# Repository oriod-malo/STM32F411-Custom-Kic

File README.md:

# STM32F411-Custom-Kit

#### NOTE (as of April 12th 2023)
#### By Kicad ERC and DRC this board should be functional however it's not manufactured yet for a physical, hands-on testing.

## Description

This is my first fully independent KiCad project after following the tutorial for the STM32F103.
A STM32F411 Discovery board was something I wanted to buy since a long time.
However, I figured out it's better if I learn to make myself something similar and have it assembled.<br>
<br>
Due to component density and pin count, this schematic ended up being a 6-layer board. <br>
<br>
Layer parameters and component choice has been made considering jlcpcb constraints and components library(for the sake of orientation). It can be manufactured by ANY service. <br>
Also feel free to change constraints / components. <br>
<br>
<br>

## Differences between this and actual Discovery Boards.

* Due to unavailability of components, I removed all the audio subsystem that Discovery boards have and replaced it with extra pins

* Again due to components availability some components have been replaced with others and / or similar components

* I have no idea how many layers Discovery Kits actually have, this one has 6 layers: Signal(F)/GND/Signal/Signal/Power/Signal(B)

## Installation
1. Create a project called "STM32 Discovery" in KiCad 7.0 (while this is NOT a Discovery kit the name persists from when I first created the project for orientation)

2. Copy all files <except for those in the (previous_sections_files)> from this Git inside the .../Documents/KiCad/7.0/projects/STM32 Discovery

3. Go to the folder "(previous_sections_files)" you will see two subfolders "3dmodels" and "footprints". Copy those in "/Documents/KiCad/7.0/3dmodels" and ""/Documents/KiCad/7.0/footprints" respectively

## Screenshoots

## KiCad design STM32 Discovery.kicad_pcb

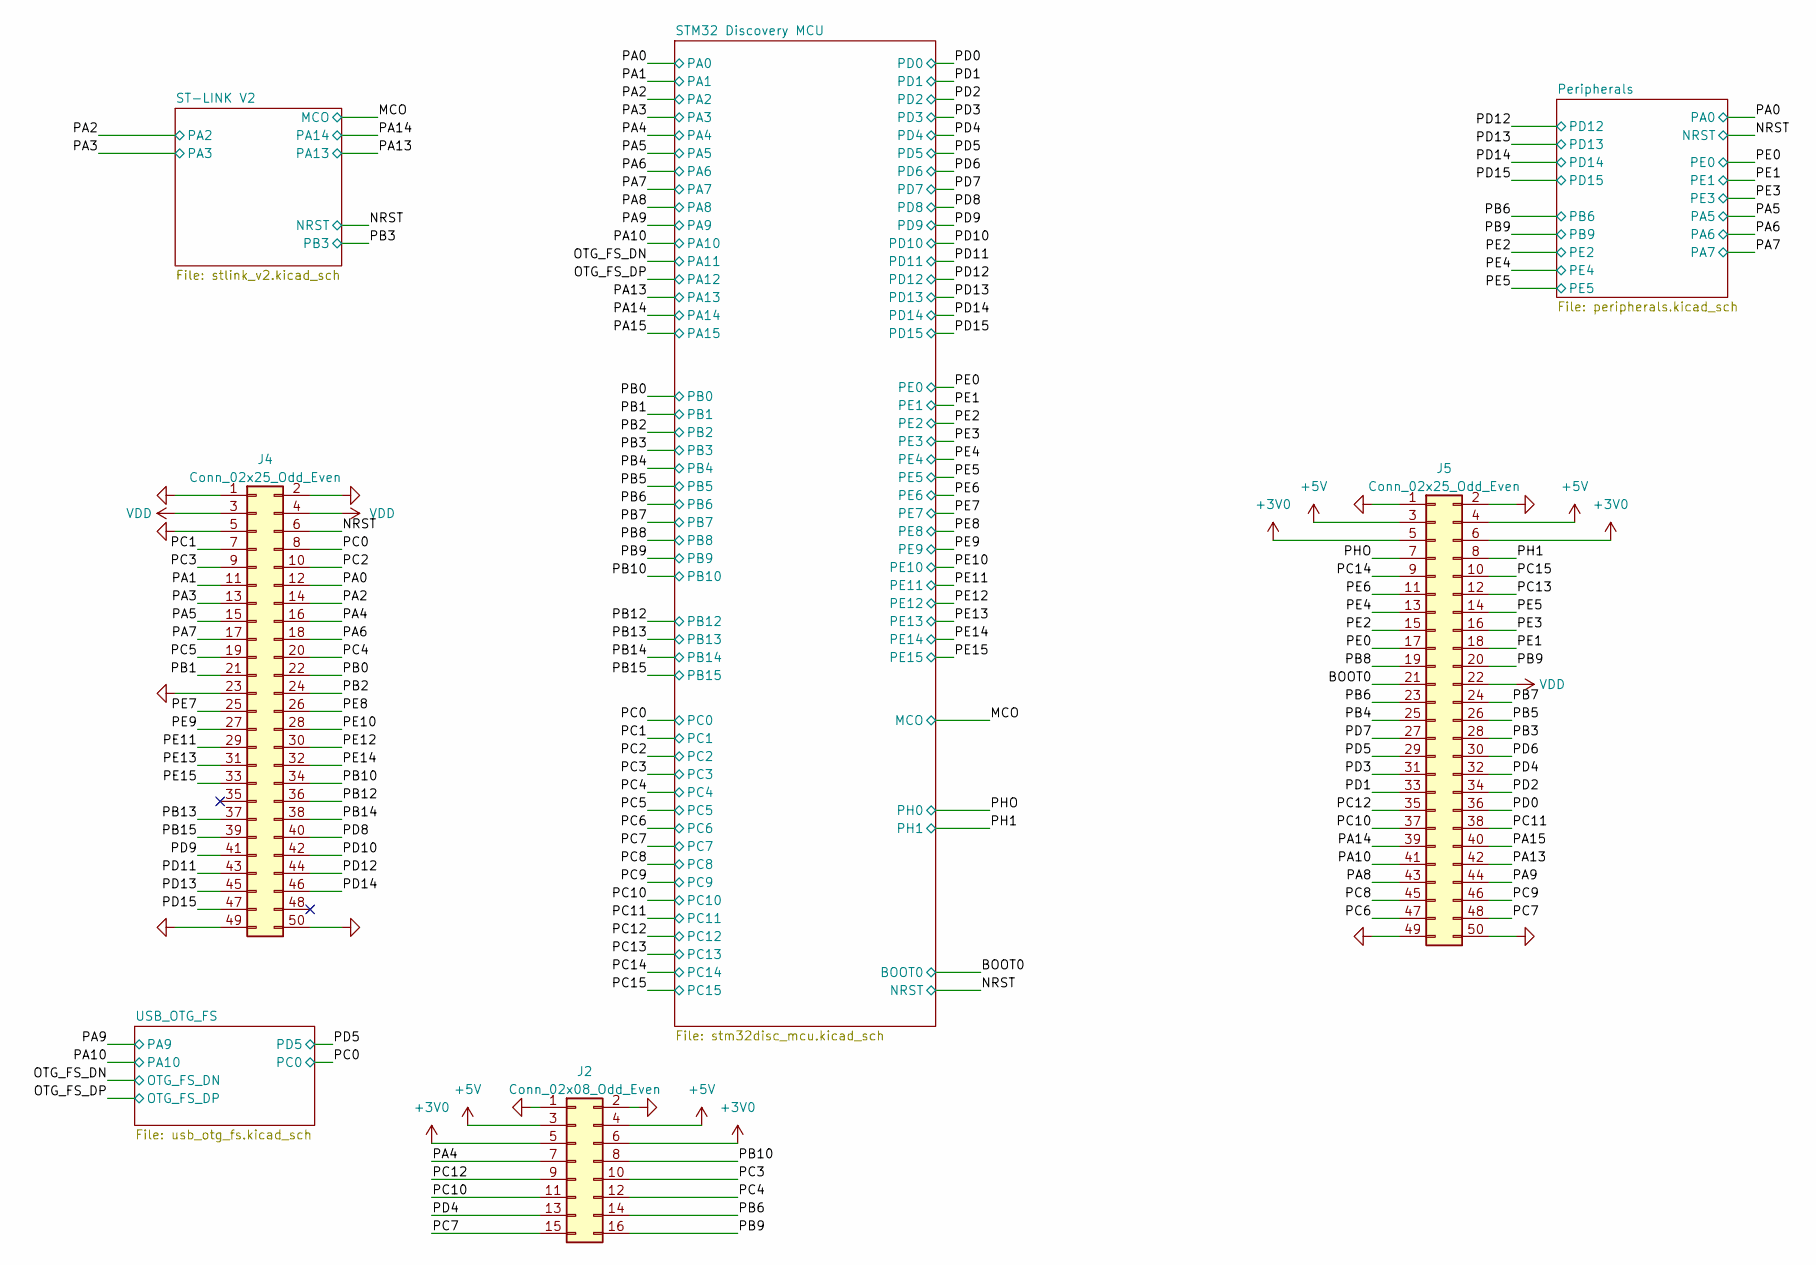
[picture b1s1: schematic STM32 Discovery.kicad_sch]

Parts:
J2: Conn_02x08_Odd_Even; PinHeader_2x08_P2.54mm_Vertical
J4, J5: Conn_02x25_Odd_Even; PinHeader_2x25_P2.54mm_Vertical

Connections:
+3V0: J2.5, J2.6, J5.5, J5.6; also elsewhere on the board
+5V: J2.3, J2.4, J5.3, J5.4; also elsewhere on the board
/BOOT0: J5.21; also elsewhere on the board
/NRST: J4.6; also elsewhere on the board
/PA0: J4.12; also elsewhere on the board
/PA1: J4.11; also elsewhere on the board
/PA2: J4.14; also elsewhere on the board
/PA3: J4.13; also elsewhere on the board
/PA4: J2.7, J4.16; also elsewhere on the board
/PA5: J4.15; also elsewhere on the board
/PA6: J4.18; also elsewhere on the board
/PA7: J4.17; also elsewhere on the board
/PA8: J5.43; also elsewhere on the board
/PA9: J5.44; also elsewhere on the board
/PA10: J5.41; also elsewhere on the board
/PA13: J5.42; also elsewhere on the board
/PA14: J5.39; also elsewhere on the board
/PA15: J5.40; also elsewhere on the board
/PB0: J4.22; also elsewhere on the board
/PB1: J4.21; also elsewhere on the board
/PB2: J4.24; also elsewhere on the board
/PB3: J5.28; also elsewhere on the board
/PB4: J5.25; also elsewhere on the board
/PB5: J5.26; also elsewhere on the board
/PB6: J2.14, J5.23; also elsewhere on the board
/PB7: J5.24; also elsewhere on the board
/PB8: J5.19; also elsewhere on the board
/PB9: J2.16, J5.20; also elsewhere on the board
/PB10: J2.8, J4.34; also elsewhere on the board
/PB12: J4.36; also elsewhere on the board
/PB13: J4.37; also elsewhere on the board
/PB14: J4.38; also elsewhere on the board
/PB15: J4.39; also elsewhere on the board
/PC0: J4.8; also elsewhere on the board
/PC1: J4.7; also elsewhere on the board
/PC2: J4.10; also elsewhere on the board
/PC3: J2.10, J4.9; also elsewhere on the board
/PC4: J2.12, J4.20; also elsewhere on the board
/PC5: J4.19; also elsewhere on the board
/PC6: J5.47; also elsewhere on the board
/PC7: J2.15, J5.48; also elsewhere on the board
/PC8: J5.45; also elsewhere on the board
/PC9: J5.46; also elsewhere on the board
/PC10: J2.11, J5.37; also elsewhere on the board
/PC11: J5.38; also elsewhere on the board
/PC12: J2.9, J5.35; also elsewhere on the board
/PC13: J5.12; also elsewhere on the board
/PC14: J5.9; also elsewhere on the board
/PC15: J5.10; also elsewhere on the board
/PD0: J5.36; also elsewhere on the board
/PD1: J5.33; also elsewhere on the board
/PD2: J5.34; also elsewhere on the board
/PD3: J5.31; also elsewhere on the board
/PD4: J2.13, J5.32; also elsewhere on the board
/PD5: J5.29; also elsewhere on the board
/PD6: J5.30; also elsewhere on the board
/PD7: J5.27; also elsewhere on the board
/PD8: J4.40; also elsewhere on the board
/PD9: J4.41; also elsewhere on the board
/PD10: J4.42; also elsewhere on the board
/PD11: J4.43; also elsewhere on the board
/PD12: J4.44; also elsewhere on the board
/PD13: J4.45; also elsewhere on the board
/PD14: J4.46; also elsewhere on the board
/PD15: J4.47; also elsewhere on the board
/PE0: J5.17; also elsewhere on the board
/PE1: J5.18; also elsewhere on the board
/PE2: J5.15; also elsewhere on the board
/PE3: J5.16; also elsewhere on the board
/PE4: J5.13; also elsewhere on the board
/PE5: J5.14; also elsewhere on the board
/PE6: J5.11; also elsewhere on the board
/PE7: J4.25; also elsewhere on the board
/PE8: J4.26; also elsewhere on the board
/PE9: J4.27; also elsewhere on the board
/PE10: J4.28; also elsewhere on the board
/PE11: J4.29; also elsewhere on the board
/PE12: J4.30; also elsewhere on the board
/PE13: J4.31; also elsewhere on the board
/PE14: J4.32; also elsewhere on the board
/PE15: J4.33; also elsewhere on the board
/PH1: J5.8; also elsewhere on the board
/PHO: J5.7; also elsewhere on the board
GND: J2.1, J2.2, J4.1, J4.2, J4.5, J4.23, J4.49, J4.50, J5.1, J5.2, J5.49, J5.50; also elsewhere on the board
VDD: J4.3, J4.4, J5.22; also elsewhere on the board

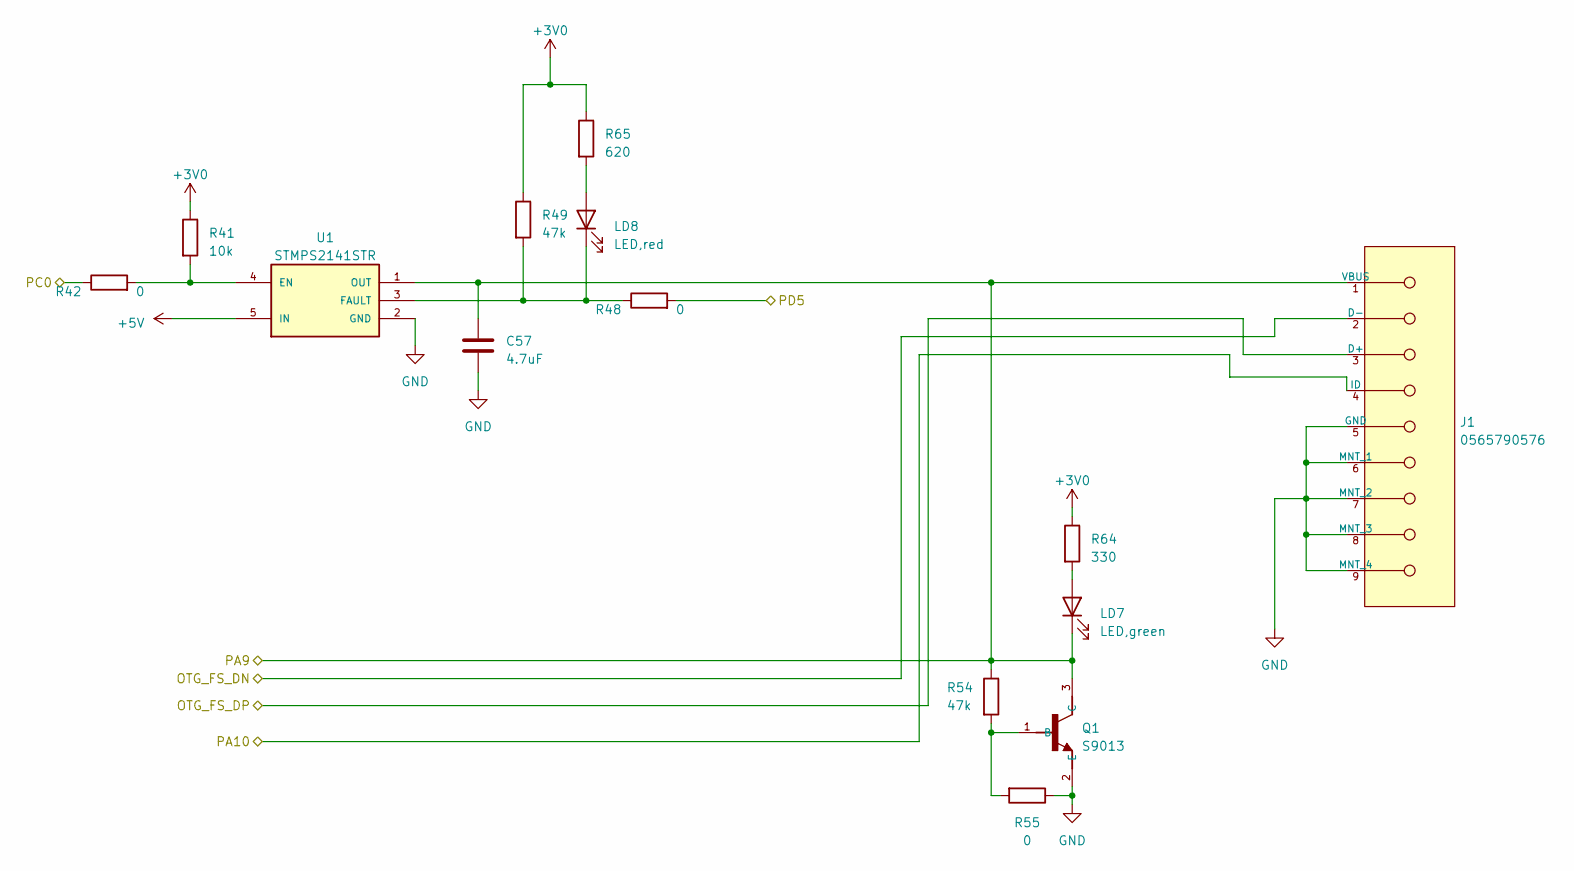
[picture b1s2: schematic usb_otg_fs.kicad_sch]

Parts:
C57: 4.7uF; C_0402_1005Metric
J1: 0565790576; Molex-0565790576-0; voltage 30VAC/DC; mouser part number 538-56579-0576; digikey description CONN RECEPT USB 5POS RT ANG SMD
LD7: LED,green; LED_0402_1005Metric
LD8: LED,red; LED_0402_1005Metric
Q1: S9013; SOT-23
R41: 10k; R_0402_1005Metric
R42, R48, R55: 0; R_0402_1005Metric
R49, R54: 47k; R_0402_1005Metric
R64: 330; R_0402_1005Metric
R65: 620; R_0402_1005Metric
U1: STMPS2141STR; SOT-23-5

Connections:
+3V0: R41.1, R49.1, R64.1, R65.1; also elsewhere on the board
+5V: U1.5 (IN); also elsewhere on the board
/OTG_FS_DN: J1.2 (D-); also elsewhere on the board
/OTG_FS_DP: J1.3 (D+); also elsewhere on the board
/PA9: C57.1, J1.1 (VBUS), LD7.1 (K), Q1.3 (C), R54.1, U1.1 (OUT); also elsewhere on the board
/PA10: J1.4 (ID); also elsewhere on the board
/PC0: R42.1; also elsewhere on the board
/PD5: R48.2; also elsewhere on the board
GND: C57.2, J1.5 (GND), J1.6 (MNT_1), J1.7 (MNT_2), J1.8 (MNT_3), J1.9 (MNT_4), Q1.2 (E), R55.1, U1.2 (GND); also elsewhere on the board
unnamed: LD7.2 (A), R64.2
unnamed: LD8.2 (A), R65.2
unnamed: LD8.1 (K), R48.1, R49.2, U1.3 (FAULT)
unnamed: Q1.1 (B), R54.2, R55.2
unnamed: R41.2, R42.2, U1.4 (EN)

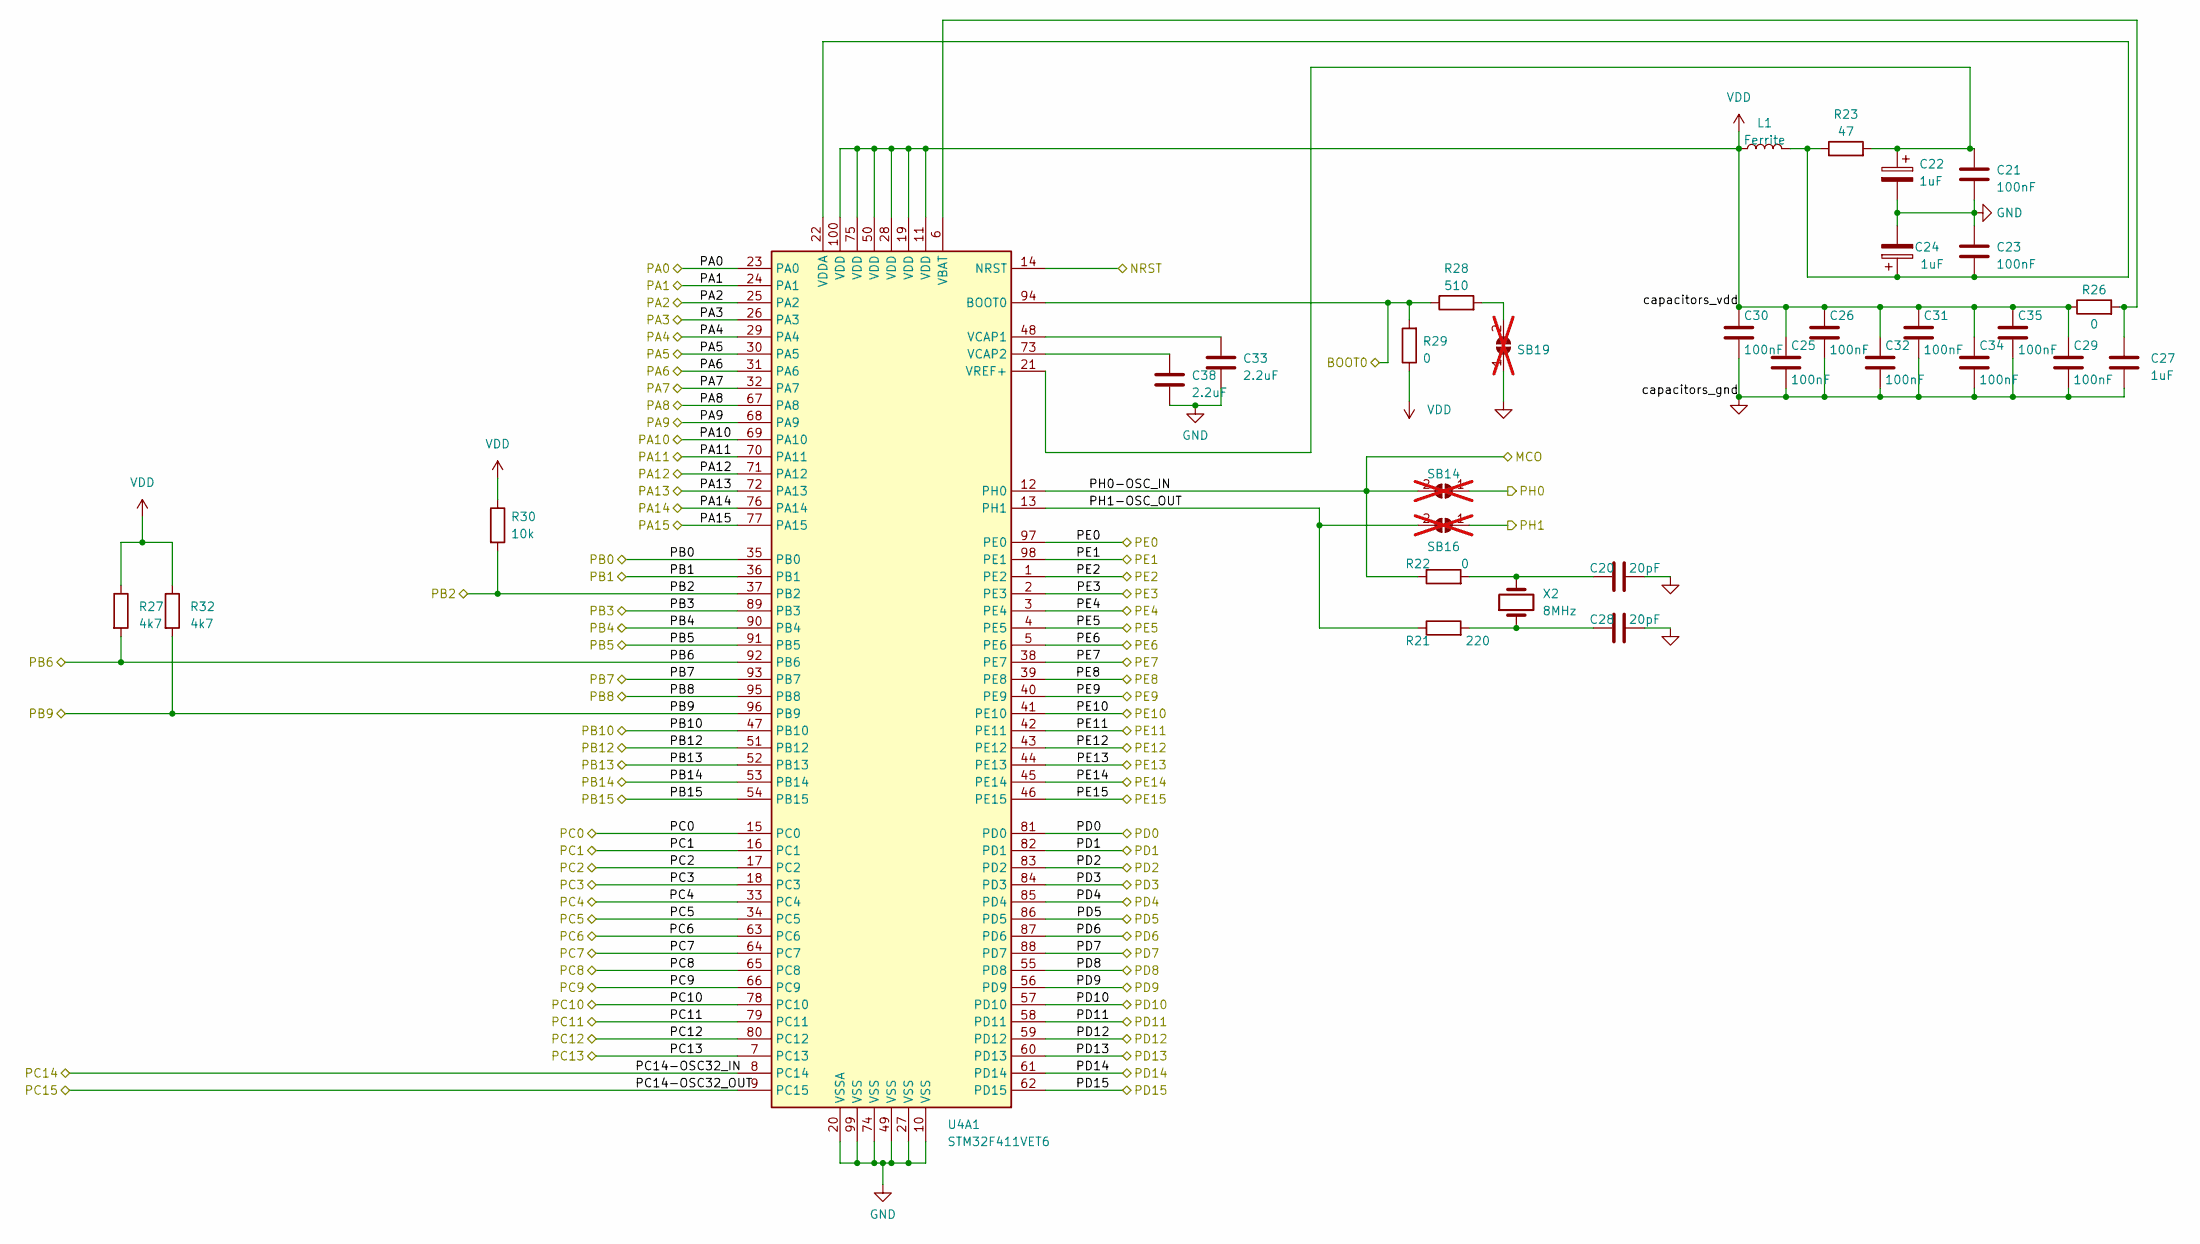
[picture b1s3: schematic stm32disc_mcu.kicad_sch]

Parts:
C20, C28: 20pF; C_0402_1005Metric
C21, C23, C25, C26, C29, C30, C31, C32, C34, C35: 100nF; C_0402_1005Metric
C22, C24, C27: 1uF; C_0402_1005Metric
C33, C38: 2.2uF; C_0402_1005Metric
L1: Ferrite; L_0603_1608Metric
R21: 220; R_0402_1005Metric
R22, R26, R29: 0; R_0402_1005Metric
R23: 47; R_0402_1005Metric
R27, R32: 4k7; R_0402_1005Metric
R28: 510; R_0402_1005Metric
R30: 10k; R_0402_1005Metric
SB14, SB16, SB19: SolderJumper_2_Open; SolderJumper-2_P1.3mm_Open_TrianglePad1.0x1.5mm; not fitted
U4A1: STM32F411VET6; LQFP-100_14x14mm_P0.5mm
X2: 8MHz; Crystal_SMD_5032-2Pin_5.0x3.2mm

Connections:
/BOOT0: R28.1, R29.2, U4A1.94 (BOOT0); also elsewhere on the board
/MCO: R22.1, SB14.2 (B), U4A1.12 (PH0); also elsewhere on the board
/NRST: U4A1.14 (NRST); also elsewhere on the board
/OTG_FS_DN: U4A1.70 (PA11); also elsewhere on the board
/OTG_FS_DP: U4A1.71 (PA12); also elsewhere on the board
/PA0: U4A1.23 (PA0); also elsewhere on the board
/PA1: U4A1.24 (PA1); also elsewhere on the board
/PA2: U4A1.25 (PA2); also elsewhere on the board
/PA3: U4A1.26 (PA3); also elsewhere on the board
/PA4: U4A1.29 (PA4); also elsewhere on the board
/PA5: U4A1.30 (PA5); also elsewhere on the board
/PA6: U4A1.31 (PA6); also elsewhere on the board
/PA7: U4A1.32 (PA7); also elsewhere on the board
/PA8: U4A1.67 (PA8); also elsewhere on the board
/PA9: U4A1.68 (PA9); also elsewhere on the board
/PA10: U4A1.69 (PA10); also elsewhere on the board
/PA13: U4A1.72 (PA13); also elsewhere on the board
/PA14: U4A1.76 (PA14); also elsewhere on the board
/PA15: U4A1.77 (PA15); also elsewhere on the board
/PB0: U4A1.35 (PB0); also elsewhere on the board
/PB1: U4A1.36 (PB1); also elsewhere on the board
/PB2: R30.2, U4A1.37 (PB2); also elsewhere on the board
/PB3: U4A1.89 (PB3); also elsewhere on the board
/PB4: U4A1.90 (PB4); also elsewhere on the board
/PB5: U4A1.91 (PB5); also elsewhere on the board
/PB6: R27.2, U4A1.92 (PB6); also elsewhere on the board
/PB7: U4A1.93 (PB7); also elsewhere on the board
/PB8: U4A1.95 (PB8); also elsewhere on the board
/PB9: R32.2, U4A1.96 (PB9); also elsewhere on the board
/PB10: U4A1.47 (PB10); also elsewhere on the board
/PB12: U4A1.51 (PB12); also elsewhere on the board
/PB13: U4A1.52 (PB13); also elsewhere on the board
/PB14: U4A1.53 (PB14); also elsewhere on the board
/PB15: U4A1.54 (PB15); also elsewhere on the board
/PC0: U4A1.15 (PC0); also elsewhere on the board
/PC1: U4A1.16 (PC1); also elsewhere on the board
/PC2: U4A1.17 (PC2); also elsewhere on the board
/PC3: U4A1.18 (PC3); also elsewhere on the board
/PC4: U4A1.33 (PC4); also elsewhere on the board
/PC5: U4A1.34 (PC5); also elsewhere on the board
/PC6: U4A1.63 (PC6); also elsewhere on the board
/PC7: U4A1.64 (PC7); also elsewhere on the board
/PC8: U4A1.65 (PC8); also elsewhere on the board
/PC9: U4A1.66 (PC9); also elsewhere on the board
/PC10: U4A1.78 (PC10); also elsewhere on the board
/PC11: U4A1.79 (PC11); also elsewhere on the board
/PC12: U4A1.80 (PC12); also elsewhere on the board
/PC13: U4A1.7 (PC13); also elsewhere on the board
/PC14: U4A1.8 (PC14); also elsewhere on the board
/PC15: U4A1.9 (PC15); also elsewhere on the board
/PD0: U4A1.81 (PD0); also elsewhere on the board
/PD1: U4A1.82 (PD1); also elsewhere on the board
/PD2: U4A1.83 (PD2); also elsewhere on the board
/PD3: U4A1.84 (PD3); also elsewhere on the board
/PD4: U4A1.85 (PD4); also elsewhere on the board
/PD5: U4A1.86 (PD5); also elsewhere on the board
/PD6: U4A1.87 (PD6); also elsewhere on the board
/PD7: U4A1.88 (PD7); also elsewhere on the board
/PD8: U4A1.55 (PD8); also elsewhere on the board
/PD9: U4A1.56 (PD9); also elsewhere on the board
/PD10: U4A1.57 (PD10); also elsewhere on the board
/PD11: U4A1.58 (PD11); also elsewhere on the board
/PD12: U4A1.59 (PD12); also elsewhere on the board
/PD13: U4A1.60 (PD13); also elsewhere on the board
/PD14: U4A1.61 (PD14); also elsewhere on the board
/PD15: U4A1.62 (PD15); also elsewhere on the board
/PE0: U4A1.97 (PE0); also elsewhere on the board
/PE1: U4A1.98 (PE1); also elsewhere on the board
/PE2: U4A1.1 (PE2); also elsewhere on the board
/PE3: U4A1.2 (PE3); also elsewhere on the board
/PE4: U4A1.3 (PE4); also elsewhere on the board
/PE5: U4A1.4 (PE5); also elsewhere on the board
/PE6: U4A1.5 (PE6); also elsewhere on the board
/PE7: U4A1.38 (PE7); also elsewhere on the board
/PE8: U4A1.39 (PE8); also elsewhere on the board
/PE9: U4A1.40 (PE9); also elsewhere on the board
/PE10: U4A1.41 (PE10); also elsewhere on the board
/PE11: U4A1.42 (PE11); also elsewhere on the board
/PE12: U4A1.43 (PE12); also elsewhere on the board
/PE13: U4A1.44 (PE13); also elsewhere on the board
/PE14: U4A1.45 (PE14); also elsewhere on the board
/PE15: U4A1.46 (PE15); also elsewhere on the board
/PH1: SB16.1 (A); also elsewhere on the board
/PHO: SB14.1 (A); also elsewhere on the board
/STM32 Discovery MCU/PH1-OSC_OUT: R21.1, SB16.2 (B), U4A1.13 (PH1)
GND: C20.2, C21.2, C22.2, C23.1, C24.2, C25.2, C26.2, C27.2, C28.2, C29.2, C30.2, C31.2, C32.2, C33.2, C34.2, C35.2, C38.2, SB19.1 (A), U4A1.10 (VSS), U4A1.20 (VSSA), U4A1.27 (VSS), U4A1.49 (VSS), U4A1.74 (VSS), U4A1.99 (VSS); also elsewhere on the board
unnamed: C20.1, R22.2, X2.2
unnamed: C28.1, R21.2, X2.1
unnamed: R28.2, SB19.2 (B)
unnamed: C27.1, R26.2, U4A1.6 (VBAT)
unnamed: C33.1, U4A1.48 (VCAP1)
unnamed: C38.1, U4A1.73 (VCAP2)
unnamed: C23.2, C24.1, L1.2, R23.1, U4A1.22 (VDDA)
unnamed: C21.1, C22.1, R23.2, U4A1.21 (VREF+)
VDD: C25.1, C26.1, C29.1, C30.1, C31.1, C32.1, C34.1, C35.1, L1.1, R26.1, R27.1, R29.1, R30.1, R32.1, U4A1.11 (VDD), U4A1.19 (VDD), U4A1.28 (VDD), U4A1.50 (VDD), U4A1.75 (VDD), U4A1.100 (VDD); also elsewhere on the board

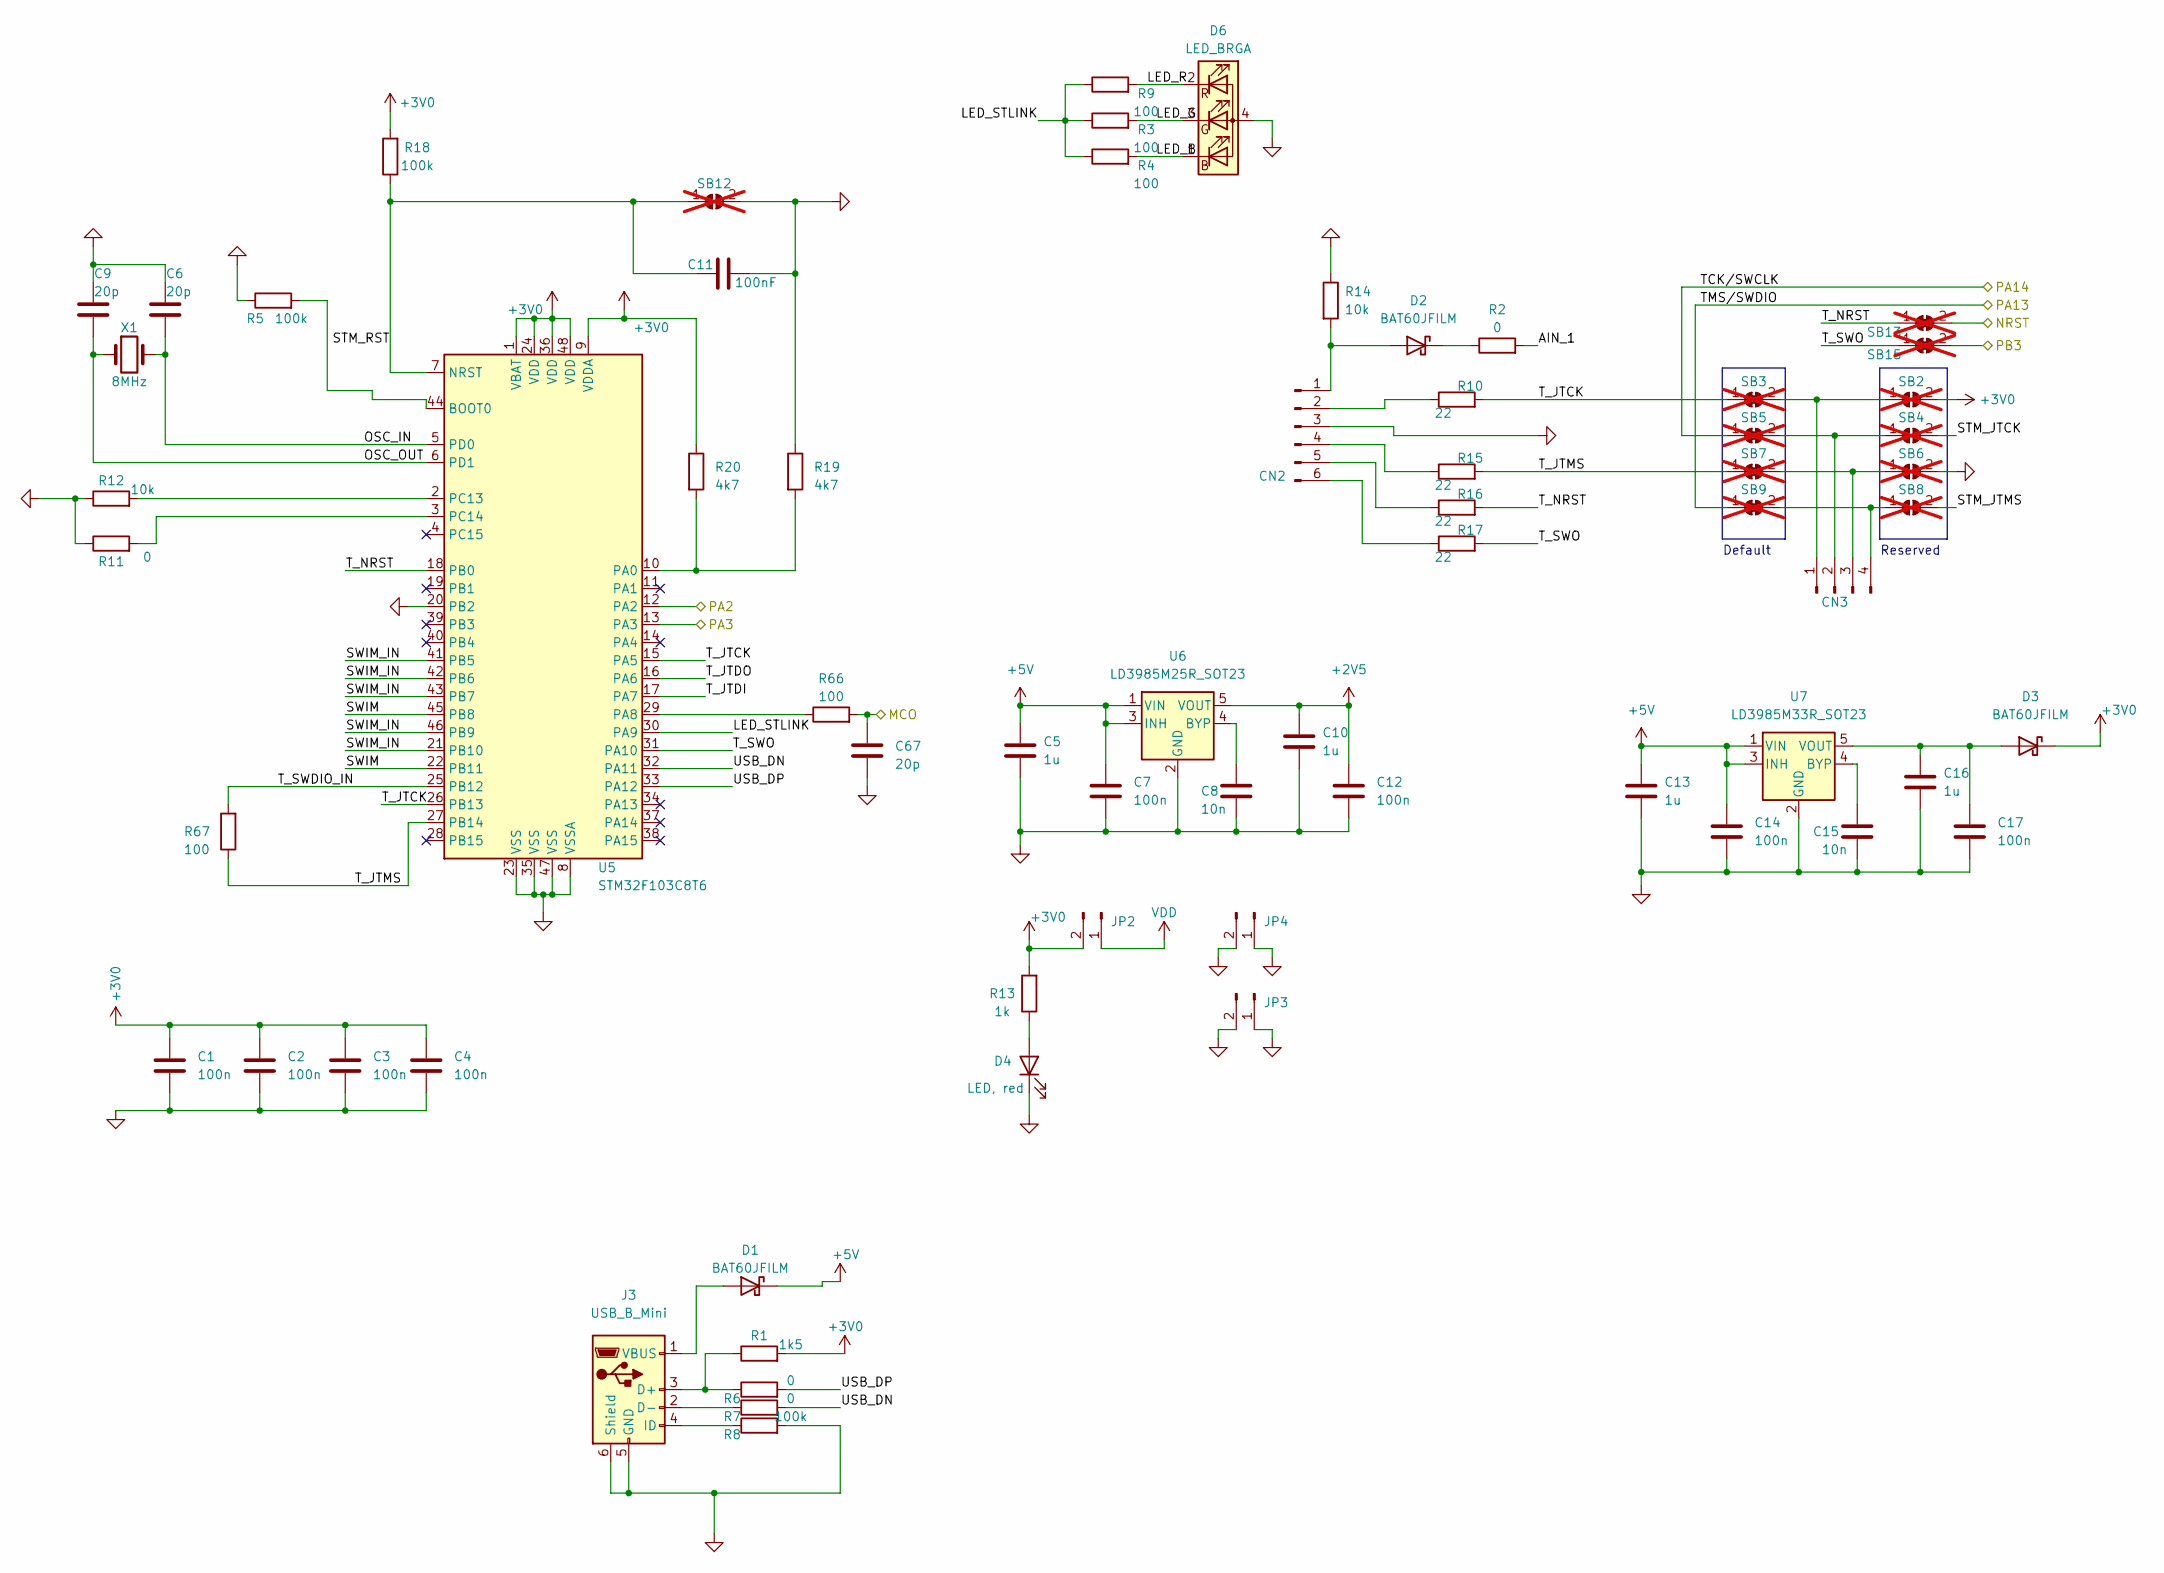
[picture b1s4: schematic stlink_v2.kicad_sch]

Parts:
C1, C2, C3, C4, C7, C12, C14, C17: 100n; C_0402_1005Metric
C5, C10, C13, C16: 1u; C_0402_1005Metric
C6, C9, C67: 20p; C_0402_1005Metric
C8, C15: 10n; C_0402_1005Metric
C11: 100nF; C_0402_1005Metric
CN2: Conn_01x06_Male; PinHeader_1x06_P2.54mm_Vertical
CN3: Conn_01x04_Male; PinHeader_1x04_P2.54mm_Vertical
D1, D2, D3: BAT60JFILM; D_SOD-323
D4: LED, red; LED_0402_1005Metric
D6: LED_BRGA; LED_LiteOn_LTST-C295K_1.6x0.8mm
J3: USB_B_Mini; USB_Mini-B_Wuerth_65100516121_Horizontal
JP2, JP3, JP4: pin jumper 2.54 1x02; PinHeader_1x02_P2.54mm_Vertical
R1: 1k5; R_0402_1005Metric
R2, R6, R7, R11: 0; R_0402_1005Metric
R3, R4, R9, R66, R67: 100; R_0402_1005Metric
R5, R8, R18: 100k; R_0402_1005Metric
R10, R15, R16, R17: 22; R_0402_1005Metric
R12, R14: 10k; R_0402_1005Metric
R13: 1k; R_0402_1005Metric
R19, R20: 4k7; R_0402_1005Metric
SB2, SB4, SB6, SB8, SB12: SolderJumper_2_Open; SolderJumper-2_P1.3mm_Open_TrianglePad1.0x1.5mm; not fitted
SB3, SB5, SB7, SB9, SB13, SB15: SolderJumper_2_Bridged; SolderJumper-2_P1.3mm_Bridged2Bar_Pad1.0x1.5mm; not fitted
U5: STM32F103C8T6; LQFP-48_7x7mm_P0.5mm
U6: LD3985M25R_SOT23; SOT-23-5
U7: LD3985M33R_SOT23; SOT-23-5
X1: 8MHz; Crystal_SMD_5032-2Pin_5.0x3.2mm

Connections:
+2V5: C10.1, C12.1, U6.5 (VOUT)
+3V0: C1.1, C2.1, C3.1, C4.1, D3.1 (K), JP2.2, R1.2, R13.2, R18.2, R20.1, SB2.2 (B), U5.1 (VBAT), U5.9 (VDDA), U5.24 (VDD), U5.36 (VDD), U5.48 (VDD); also elsewhere on the board
+5V: C5.1, C7.1, C13.1, C14.1, D1.1 (K), U6.1 (VIN), U6.3 (INH), U7.1 (VIN), U7.3 (INH); also elsewhere on the board
/MCO: C67.1, R66.2; also elsewhere on the board
/NRST: SB13.2 (B); also elsewhere on the board
/PA2: U5.12 (PA2); also elsewhere on the board
/PA3: U5.13 (PA3); also elsewhere on the board
/PA13: SB9.1 (A); also elsewhere on the board
/PA14: SB5.1 (A); also elsewhere on the board
/PB3: SB15.2 (B); also elsewhere on the board
/ST-LINK V2/AIN_1: R2.2
/ST-LINK V2/LED_B: D6.1 (BK), R4.2
/ST-LINK V2/LED_G: D6.3 (GK), R3.2
/ST-LINK V2/LED_R: D6.2 (RK), R9.2
/ST-LINK V2/LED_STLINK: R3.1, R4.1, R9.1, U5.30 (PA9)
/ST-LINK V2/OSC_IN: C6.2, U5.5 (PD0), X1.2
/ST-LINK V2/OSC_OUT: C9.2, U5.6 (PD1), X1.1
/ST-LINK V2/STM_JTCK: SB4.2 (B)
/ST-LINK V2/STM_JTMS: SB8.2 (B)
/ST-LINK V2/STM_RST: C11.1, R18.1, SB12.1 (A), U5.7 (NRST)
/ST-LINK V2/SWIM: U5.22 (PB11), U5.45 (PB8)
/ST-LINK V2/SWIM_IN: U5.21 (PB10), U5.41 (PB5), U5.42 (PB6), U5.43 (PB7), U5.46 (PB9)
/ST-LINK V2/T_JTCK: R10.2, SB3.1 (A), U5.15 (PA5), U5.26 (PB13)
/ST-LINK V2/T_JTDI: U5.17 (PA7)
/ST-LINK V2/T_JTDO: U5.16 (PA6)
/ST-LINK V2/T_JTMS: R15.2, R67.1, SB7.1 (A), U5.27 (PB14)
/ST-LINK V2/T_NRST: R16.2, SB13.1 (A), U5.18 (PB0)
/ST-LINK V2/T_SWDIO_IN: R67.2, U5.25 (PB12)
/ST-LINK V2/T_SWO: R17.2, SB15.1 (A), U5.31 (PA10)
/ST-LINK V2/USB_DN: R7.2, U5.32 (PA11)
/ST-LINK V2/USB_DP: R6.2, U5.33 (PA12)
GND: C1.2, C2.2, C3.2, C4.2, C5.2, C6.1, C7.2, C8.2, C9.1, C10.2, C11.2, C12.2, C13.2, C14.2, C15.2, C16.2, C17.2, C67.2, CN2.3, D4.1 (K), D6.4 (A), J3.5 (GND), J3.6 (Shield), JP3.1, JP3.2, JP4.1, JP4.2, R5.1, R8.2, R11.1, R12.1, R14.1, R19.1, SB6.2 (B), SB12.2 (B), U5.8 (VSSA), U5.20 (PB2), U5.23 (VSS), U5.35 (VSS), U5.47 (VSS), U6.2 (GND), U7.2 (GND); also elsewhere on the board
unnamed: CN2.1, D2.2 (A), R14.2
unnamed: CN2.2, R10.1
unnamed: CN2.4, R15.1
unnamed: CN2.5, R16.1
unnamed: CN2.6, R17.1
unnamed: CN3.1, SB2.1 (A), SB3.2 (B)
unnamed: CN3.2, SB4.1 (A), SB5.2 (B)
unnamed: CN3.3, SB6.1 (A), SB7.2 (B)
unnamed: CN3.4, SB8.1 (A), SB9.2 (B)
unnamed: D1.2 (A), J3.1 (VBUS)
unnamed: D2.1 (K), R2.1
unnamed: C16.1, C17.1, D3.2 (A), U7.5 (VOUT)
unnamed: D4.2 (A), R13.1
unnamed: J3.3 (D+), R1.1, R6.1
unnamed: J3.2 (D-), R7.1
unnamed: J3.4 (ID), R8.1
unnamed: R5.2, U5.44 (BOOT0)
unnamed: R19.2, R20.2, U5.10 (PA0)
unnamed: R66.1, U5.29 (PA8)
unnamed: R12.2, U5.2 (PC13)
unnamed: R11.2, U5.3 (PC14)
unnamed: C8.1, U6.4 (BYP)
unnamed: C15.1, U7.4 (BYP)
VDD: JP2.1; also elsewhere on the board

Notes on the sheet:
Default
Reserved
